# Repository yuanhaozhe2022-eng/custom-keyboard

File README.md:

# custom-keyboard

AI Disclosure:
During this project, I ONLY used AI to move files around inside the repo in order to fit the shipping requirement such as moving the bom.csv out of the folder into the root.

Hi, my name is Eric and this is my submission on the Hack Club KEEB project.

Short description:
It's a split, 65%-style mechanical keyboard with an integrated plate, split spacebar, rotary encoder, custom PCB and a small OLED display. Firmware runs on RMK.

Specs:
- MCU: Raspberry Pi Pico (RP2040)
- Matrix: 5 rows x 13~14 columns, wired matrix
- Layout: split 65% in one case, both halves wired directly to a single Pico (no wireless link for now)
- Extras: rotary encoder (volume control), 0.91" OLED (I2C)
- Case: integrated plate, 3D printed in PETG (~230g), reserved space for future add-ons
- Firmware: RMK, built via GitHub Actions cloud compilation

Rendered Pictures:

Link to [Onshape](https://cad.onshape.com/documents/044ff0b7861f7575dc804a4a/w/e4834b19a17e51af50c75ed1/e/4311a3e3683cd25e4222572f?renderMode=0&uiState=6ade9b22ddd00cc3e574c277)

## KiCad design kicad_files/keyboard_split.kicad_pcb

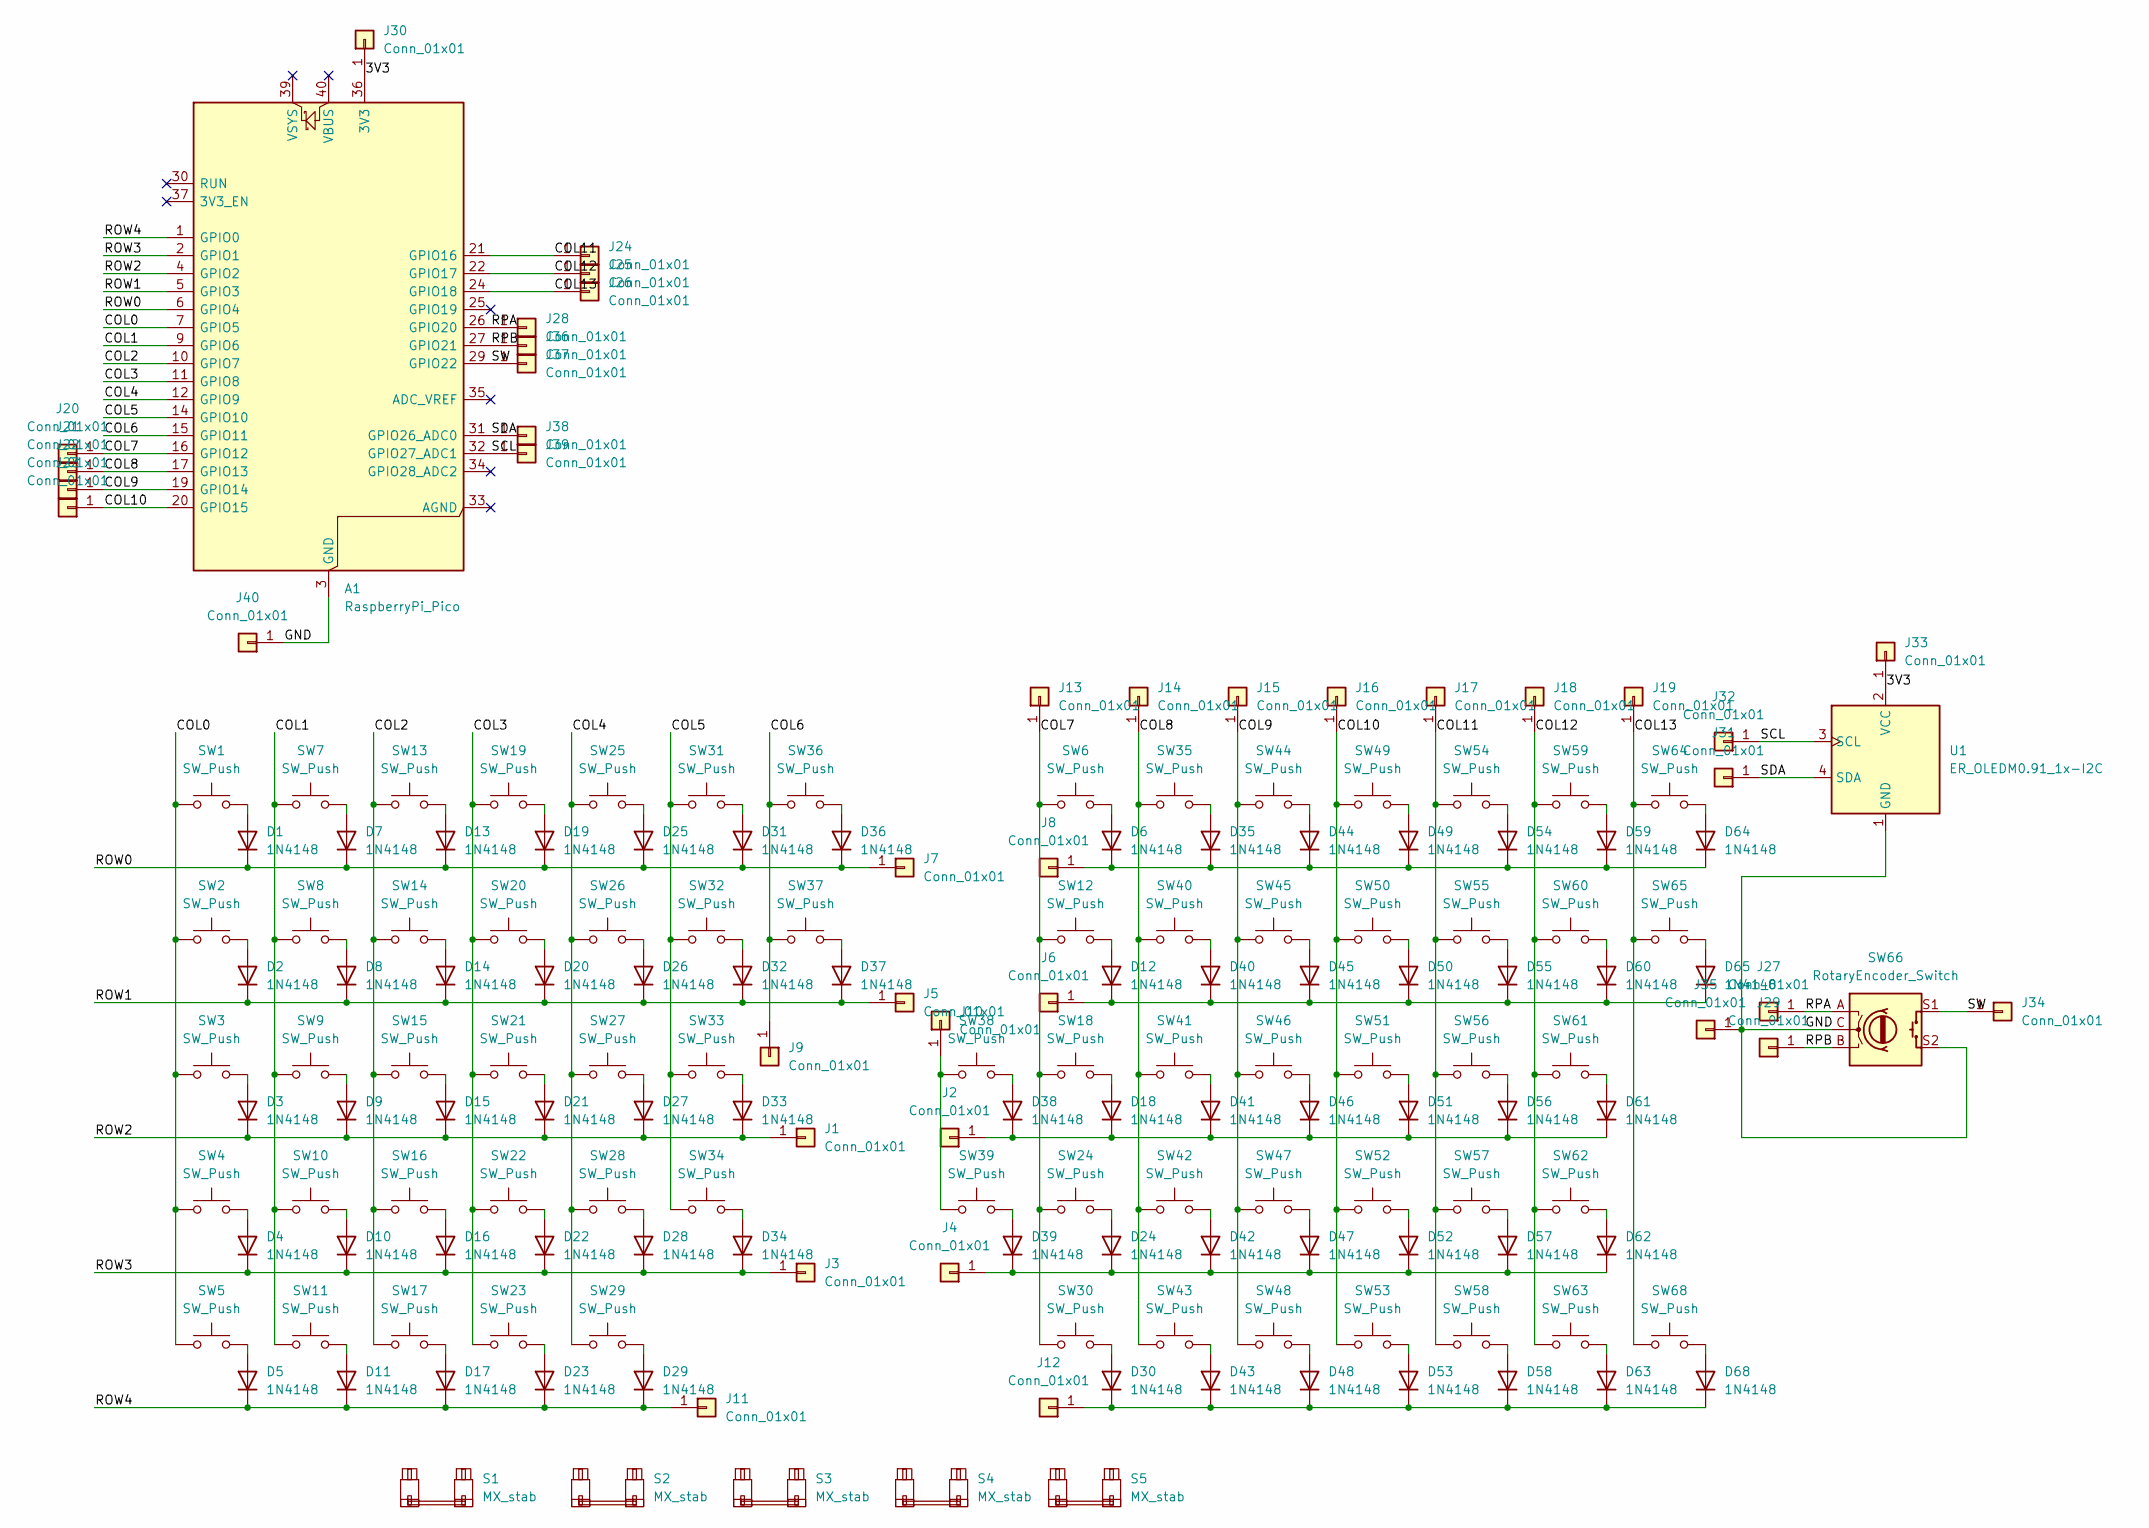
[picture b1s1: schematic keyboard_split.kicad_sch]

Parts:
A1: RaspberryPi_Pico; RaspberryPi_Pico_Common_THT
D1, D2, D3, D4, D5, D6, D7, D8, D9, D10, D11, D12, D13, D14, D15, D16, D17, D18, D19, D20, D21, D22, D23, D24, D25, D26, D27, D28, D29, D30, D31, D32, D33, D34, D35, D36, D37, D38, D39, D40, D41, D42, D43, D44, D45, D46, D47, D48, D49, D50, D51, D52, D53, D54, D55, D56, D57, D58, D59, D60, D61, D62, D63, D64, D65, D68: 1N4148; D_DO-35_SOD27_P7.62mm_Horizontal
J1, J2, J3, J4, J5, J6, J7, J8, J9, J10, J11, J12, J13, J14, J15, J16, J17, J18, J19, J20, J21, J22, J23, J24, J25, J26, J27, J28, J29, J30, J31, J32, J33, J34, J35, J36, J37, J38, J39, J40: Conn_01x01; SolderWire-1sqmm_1x01_D1.4mm_OD2.7mm
S1, S2, S3, S4, S5: MX_stab; STAB_MX_2u
SW1, SW2, SW3, SW4, SW5, SW6, SW7, SW8, SW9, SW10, SW11, SW12, SW13, SW14, SW15, SW16, SW17, SW18, SW19, SW20, SW21, SW22, SW23, SW24, SW25, SW26, SW27, SW28, SW29, SW30, SW31, SW32, SW33, SW34, SW35, SW36, SW37, SW38, SW39, SW40, SW41, SW42, SW43, SW44, SW45, SW46, SW47, SW48, SW49, SW50, SW51, SW52, SW53, SW54, SW55, SW56, SW57, SW58, SW59, SW60, SW61, SW62, SW63, SW64, SW65, SW68: SW_Push; SW_MX_1u
SW66: RotaryEncoder_Switch; RotaryEncoder_Alps_EC11E-Switch_Vertical_H20mm
U1: ER_OLEDM0.91_1x-I2C

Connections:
/COL0: A1.7 (GPIO5), SW1.1, SW2.1, SW3.1, SW4.1, SW5.1
/COL1: A1.9 (GPIO6), SW7.1, SW8.1, SW9.1, SW10.1, SW11.1
/COL2: A1.10 (GPIO7), SW13.1, SW14.1, SW15.1, SW16.1, SW17.1
/COL3: A1.11 (GPIO8), SW19.1, SW20.1, SW21.1, SW22.1, SW23.1
/COL4: A1.12 (GPIO9), SW25.1, SW26.1, SW27.1, SW28.1, SW29.1
/COL5: A1.14 (GPIO10), SW31.1, SW32.1, SW33.1, SW34.1
/COL6: A1.15 (GPIO11), J9.1 (Pin_1_1), SW36.1, SW37.1
/COL7: A1.16 (GPIO12), J13.1 (Pin_1_1), J20.1 (Pin_1_1), SW6.1, SW12.1, SW18.1, SW24.1, SW30.1
/COL8: A1.17 (GPIO13), J14.1 (Pin_1_1), J21.1 (Pin_1_1), SW35.1, SW40.1, SW41.1, SW42.1, SW43.1
/COL9: A1.19 (GPIO14), J15.1 (Pin_1_1), J22.1 (Pin_1_1), SW44.1, SW45.1, SW46.1, SW47.1, SW48.1
/COL10: A1.20 (GPIO15), J16.1 (Pin_1_1), J23.1 (Pin_1_1), SW49.1, SW50.1, SW51.1, SW52.1, SW53.1
/COL11: A1.21 (GPIO16), J17.1 (Pin_1_1), J24.1 (Pin_1_1), SW54.1, SW55.1, SW56.1, SW57.1, SW58.1
/COL12: A1.22 (GPIO17), J18.1 (Pin_1_1), J25.1 (Pin_1_1), SW59.1, SW60.1, SW61.1, SW62.1, SW63.1
/COL13: A1.24 (GPIO18), J19.1 (Pin_1_1), J26.1 (Pin_1_1), SW64.1, SW65.1, SW68.1
/ROW0: A1.6 (GPIO4), D1.1 (K), D7.1 (K), D13.1 (K), D19.1 (K), D25.1 (K), D31.1 (K), D36.1 (K), J7.1 (Pin_1_1)
/ROW1: A1.5 (GPIO3), D2.1 (K), D8.1 (K), D14.1 (K), D20.1 (K), D26.1 (K), D32.1 (K), D37.1 (K), J5.1 (Pin_1_1)
/ROW2: A1.4 (GPIO2), D3.1 (K), D9.1 (K), D15.1 (K), D21.1 (K), D27.1 (K), D33.1 (K), J1.1 (Pin_1_1)
/ROW3: A1.2 (GPIO1), D4.1 (K), D10.1 (K), D16.1 (K), D22.1 (K), D28.1 (K), D34.1 (K), J3.1 (Pin_1_1)
/ROW4: A1.1 (GPIO0), D5.1 (K), D11.1 (K), D17.1 (K), D23.1 (K), D29.1 (K), J11.1 (Pin_1_1)
/RPA: A1.26 (GPIO20), J27.1 (Pin_1_1), J28.1 (Pin_1_1), SW66.A
/RPB: A1.27 (GPIO21), J29.1 (Pin_1_1), J36.1 (Pin_1_1), SW66.B
/SCL: A1.32 (GPIO27_ADC1), J32.1 (Pin_1_1), J39.1 (Pin_1_1), U1.3 (SCL)
/SDA: A1.31 (GPIO26_ADC0), J31.1 (Pin_1_1), J38.1 (Pin_1_1), U1.4 (SDA)
/SW: A1.29 (GPIO22), J34.1 (Pin_1_1), J37.1 (Pin_1_1), SW66.S1
unnamed: D1.2 (A), SW1.2
unnamed: D2.2 (A), SW2.2
unnamed: D3.2 (A), SW3.2
unnamed: D4.2 (A), SW4.2
unnamed: D5.2 (A), SW5.2
unnamed: D6.2 (A), SW6.2
unnamed: D7.2 (A), SW7.2
unnamed: D8.2 (A), SW8.2
unnamed: D9.2 (A), SW9.2
unnamed: D10.2 (A), SW10.2
unnamed: D11.2 (A), SW11.2
unnamed: D12.2 (A), SW12.2
unnamed: D12.1 (K), D40.1 (K), D45.1 (K), D50.1 (K), D55.1 (K), D60.1 (K), D65.1 (K), J6.1 (Pin_1_1)
unnamed: D13.2 (A), SW13.2
unnamed: D14.2 (A), SW14.2
unnamed: D15.2 (A), SW15.2
unnamed: D16.2 (A), SW16.2
unnamed: D17.2 (A), SW17.2
unnamed: D18.2 (A), SW18.2
unnamed: D18.1 (K), D38.1 (K), D41.1 (K), D46.1 (K), D51.1 (K), D56.1 (K), D61.1 (K), J2.1 (Pin_1_1)
unnamed: D19.2 (A), SW19.2
unnamed: D20.2 (A), SW20.2
unnamed: D21.2 (A), SW21.2
unnamed: D22.2 (A), SW22.2
unnamed: D23.2 (A), SW23.2
unnamed: D24.2 (A), SW24.2
unnamed: D24.1 (K), D39.1 (K), D42.1 (K), D47.1 (K), D52.1 (K), D57.1 (K), D62.1 (K), J4.1 (Pin_1_1)
unnamed: D25.2 (A), SW25.2
unnamed: D26.2 (A), SW26.2
unnamed: D27.2 (A), SW27.2
unnamed: D28.2 (A), SW28.2
unnamed: D29.2 (A), SW29.2
unnamed: D30.2 (A), SW30.2
unnamed: D30.1 (K), D43.1 (K), D48.1 (K), D53.1 (K), D58.1 (K), D63.1 (K), D68.1 (K), J12.1 (Pin_1_1)
unnamed: D31.2 (A), SW31.2
unnamed: D32.2 (A), SW32.2
unnamed: D33.2 (A), SW33.2
unnamed: D34.2 (A), SW34.2
unnamed: D35.2 (A), SW35.2
unnamed: D6.1 (K), D35.1 (K), D44.1 (K), D49.1 (K), D54.1 (K), D59.1 (K), D64.1 (K), J8.1 (Pin_1_1)
unnamed: D36.2 (A), SW36.2
unnamed: D37.2 (A), SW37.2
unnamed: D38.2 (A), SW38.2
unnamed: D39.2 (A), SW39.2
unnamed: D40.2 (A), SW40.2
unnamed: D41.2 (A), SW41.2
unnamed: D42.2 (A), SW42.2
unnamed: D43.2 (A), SW43.2
unnamed: D44.2 (A), SW44.2
unnamed: D45.2 (A), SW45.2
unnamed: D46.2 (A), SW46.2
unnamed: D47.2 (A), SW47.2
unnamed: D48.2 (A), SW48.2
unnamed: D49.2 (A), SW49.2
unnamed: D50.2 (A), SW50.2
unnamed: D51.2 (A), SW51.2
unnamed: D52.2 (A), SW52.2
unnamed: D53.2 (A), SW53.2
unnamed: D54.2 (A), SW54.2
unnamed: D55.2 (A), SW55.2
unnamed: D56.2 (A), SW56.2
unnamed: D57.2 (A), SW57.2
unnamed: D58.2 (A), SW58.2
unnamed: D59.2 (A), SW59.2
unnamed: D60.2 (A), SW60.2
unnamed: D61.2 (A), SW61.2
unnamed: D62.2 (A), SW62.2
unnamed: D63.2 (A), SW63.2
unnamed: D64.2 (A), SW64.2
unnamed: D65.2 (A), SW65.2
unnamed: D68.2 (A), SW68.2
unnamed: J10.1 (Pin_1_1), SW38.1, SW39.1

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
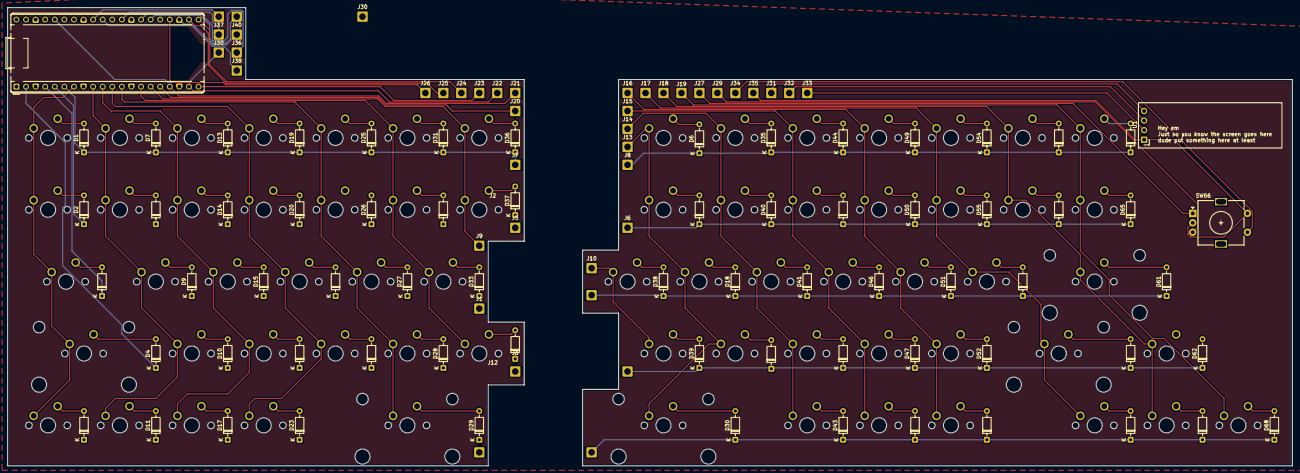
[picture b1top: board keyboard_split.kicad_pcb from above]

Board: 2 copper layers, 340.5 x 121.4 mm, 181 parts (0 on the bottom side), 98 nets.

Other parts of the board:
J30#2: Conn_01x01; SolderWire-1sqmm_1x01_D1.4mm_OD2.7mm
S6, S7: MX_stab; STAB_MX_2u

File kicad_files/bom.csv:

"Reference","Qty","Value","DNP","Exclude from BOM","Exclude from Board","Exclude from Simulation","Exclude from Position Files","Footprint","Datasheet"
"A1","1","RaspberryPi_Pico","","","","","${EXCLUDE_FROM_POS_FILES}","Module:RaspberryPi_Pico_Common_THT","https://datasheets.raspberrypi.com/pico/pico-datasheet.pdf"
"D1,D2,D3,D4,D5,D6,D7,D8,D9,D10,D11,D12,D13,D14,D15,D16,D17,D18,D19,D20,D21,D22,D23,D24,D25,D26,D27,D28,D29,D30,D31,D32,D33,D34,D35,D36,D37,D38,D39,D40,D41,D42,D43,D44,D45,D46,D47,D48,D49,D50,D51,D52,D53,D54,D55,D56,D57,D58,D59,D60,D61,D62,D63,D64,D65,D68","66","1N4148","","","","","${EXCLUDE_FROM_POS_FILES}","Diode_THT:D_DO-35_SOD27_P7.62mm_Horizontal","https://assets.nexperia.com/documents/data-sheet/1N4148_1N4448.pdf"
"J1,J2,J3,J4,J5,J6,J7,J8,J9,J10,J11,J12,J13,J14,J15,J16,J17,J18,J19,J20,J21,J22,J23,J24,J25,J26,J27,J28,J29,J30,J31,J32,J33,J34,J35,J36,J37,J38,J39,J40","40","Conn_01x01","","","","","${EXCLUDE_FROM_POS_FILES}","Connector_Wire:SolderWire-1sqmm_1x01_D1.4mm_OD2.7mm",""
"S1,S2,S3,S4,S5","5","MX_stab","","","","","${EXCLUDE_FROM_POS_FILES}","PCM_marbastlib-mx:STAB_MX_2u",""
"SW1,SW2,SW3,SW4,SW5,SW6,SW7,SW8,SW9,SW10,SW11,SW12,SW13,SW14,SW15,SW16,SW17,SW18,SW19,SW20,SW21,SW22,SW23,SW24,SW25,SW26,SW27,SW28,SW29,SW30,SW31,SW32,SW33,SW34,SW35,SW36,SW37,SW38,SW39,SW40,SW41,SW42,SW43,SW44,SW45,SW46,SW47,SW48,SW49,SW50,SW51,SW52,SW53,SW54,SW55,SW56,SW57,SW58,SW59,SW60,SW61,SW62,SW63,SW64,SW65,SW68","66","SW_Push","","","","","${EXCLUDE_FROM_POS_FILES}","PCM_marbastlib-mx:SW_MX_1u",""
"SW66","1","RotaryEncoder_Switch","","","","","${EXCLUDE_FROM_POS_FILES}","Rotary_Encoder:RotaryEncoder_Alps_EC11E-Switch_Vertical_H20mm",""
"U1","1","ER_OLEDM0.91_1x-I2C","","","","","${EXCLUDE_FROM_POS_FILES}","Display:ER_OLEDM0.91_1x-I2C","https://www.buydisplay.com/download/manual/ER-OLEDM0.91-1_Da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"
